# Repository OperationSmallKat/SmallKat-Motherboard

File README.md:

# Esp32-S3 Motherboard

## Pins
|Pin|Use|
|---|---|
| 0| Boot|
| 1| Servo 15|
| 2| Servo 14|
| 3| Servo 13|
| 4| Servo 12|
| 5| Fuse 4 ADC|
| 6| Fuse 1 ADC|
| 7| Servo 0|
| 8| Servo 1|
| 9| Servo 2|
| 10| Servo 3|
| 11| Fuse 2 ADC|
| 12| Servo 4|
| 13| Servo 5|
| 14| Servo 6|
| 15| 6V ADC|
| 16| Batt Voltage ADC|
| 17| Fuse 3 ADC|
| 18| Fuse 5 ADC|
| 19| USB -|
| 20| USB +|
| 21| Servo 7|
| 26| AD Servo 1|
| 33| AD Servo 3|
| 34| AD Servo 4|
| 35| Batt Serial TX|
| 36| Heart Beat LED|
| 37| Servo 8|
| 38| Servo 9|
| 39| Servo 10|
| 40| Servo 11|
| 41| SDA|
| 42| SCL|
| 43| TX|
| 44| RX|
| 45| |
| 46| |
| 47| AD Servo 2|
| 48| Batt Serial RX|

## I2C

  * i2c (SCL 42, SDA 41) - BNO055

## Serial 
  * Serial 0: Tx 43, Rx 44
  * Serial 1: Tx 35, Rx 48

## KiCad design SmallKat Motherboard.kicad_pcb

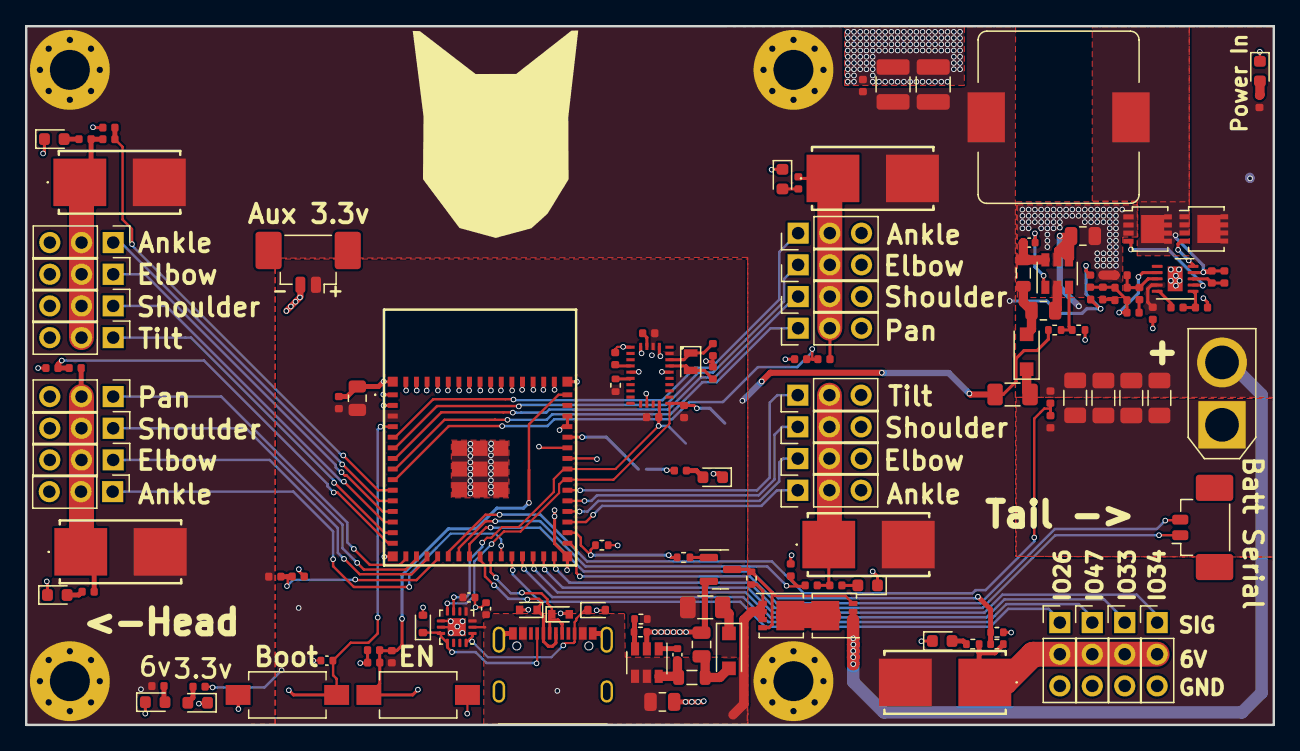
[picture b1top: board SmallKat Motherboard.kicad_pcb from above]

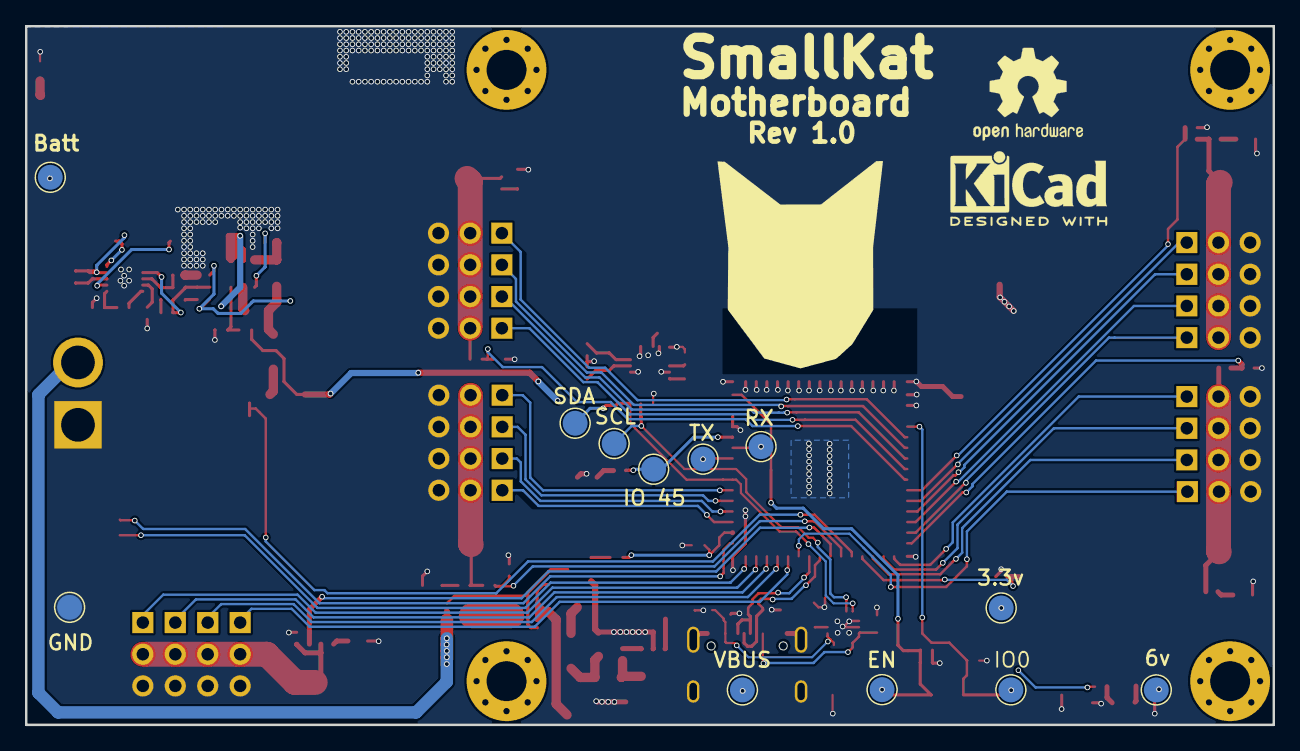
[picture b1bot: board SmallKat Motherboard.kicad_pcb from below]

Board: 2 copper layers, 100.0 x 56.0 mm, 150 parts (12 on the bottom side), 88 nets.

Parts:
AC1: BNO055; BNO085
C1, C3, C12, C14, C18, C22, C23: 0.1uF; C_0402_1005Metric
C2, C5: 2.2uF; C_0805_2012Metric
C4, C6: 10uF; C_0805_2012Metric
C7: 0.1μF; C_0402_1005Metric
C8: 1μF; C_0402_1005Metric
C15, C16: 10pF; C_0402_1005Metric
C17: 22uF; C_0805_2012Metric
C24: 1000pF; C_0402_1005Metric
C25: 100pF; C_0402_1005Metric
C26: 10nF; C_0402_1005Metric
C27, C36: 1uF; C_0402_1005Metric
C28: 4.7uF; C_0402_1005Metric
C29: 470nF; C_0402_1005Metric
C30, C32: 10uF; C_1206_3216Metric
C31, C34: 47uF; C_1206_3216Metric
C33, C35: 100uF; C_1210_3225Metric
D1, D2, D3, D6, D9, D10, D11, D12, D13: LED; LED_0603_1608Metric
D4, D5: DIODE; D_SOD-123F
D7, D8, D14, D17: D_TVS; D_SOD-523
F1, F2, F3, F4, F5: Fuse; 0154500DRTL
F6, F7: Fuse; Fuse_1206_3216Metric
H1, H2, H3, H4: MountingHole_Pad; MountingHole_3.2mm_M3_Pad_Via
IC1, IC2: LMR14010A; SOT-23-6
IC3: TPS40192DRCT-TPS40192DRCT; VSON-10-1EP_3x3mm_P0.5mm_EP1.2x2mm
IC4: ESP32-S3-MINI-1-N8; ESP32S3MINI1N8
J1, J2: BATT_SERIAL; Molex_PicoBlade_53398-0271_1x02-1MP_P1.25mm_Vertical
J3, J4, J5, J6, J9, J10, J11, J12, J13, J14, J15, J16, J17, J18, J19, J20, J21, J22, J23, J24: Conn_01x03_Male; PinHeader_1x03_P2.54mm_Vertical
J8: USB_C_Receptacle; C167321
J25: Conn_01x02_Female; AMASS_XT30U-F_1x02_P5.0mm_Vertical
L1, L2: 10uH; L_0805_2012Metric
L3: 1uH; L_Bourns_SRP1245A
Q1: MMBT3904; SOT-23
Q2, Q3: AON7262E; LFPAK33
Q4, Q5: DMP3017SFG; Diodes_PowerDI3333-8
R1, R16: 330R; R_0402_1005Metric
R2, R4, R7, R10, R13, R15, R17, R19, R20, R23, R24, R27, R30, R33: 10K; R_0402_1005Metric
R3: 2.18K; R_0402_1005Metric
R5, R8, R25, R28, R31, R34: 8.2K; R_0402_1005Metric
R6: 120K; R_0402_1005Metric
R9, R26, R29, R32, R35: 20K; R_0402_1005Metric
R11, R12: 33.2K; R_0402_1005Metric
R21: 10kΩ; R_0402_1005Metric
R22: 2kΩ; R_0402_1005Metric
R36: 2.18k; R_0402_1005Metric
R37: 20k; R_0402_1005Metric
R38: 2.61k; R_0402_1005Metric
R39: 4.22k; R_0402_1005Metric
R40: 12k; R_0402_1005Metric
R41, R42: 100k; R_0402_1005Metric
R43: 1K; R_0402_1005Metric
R44: 100kΩ; R_0402_1005Metric
SW1, SW2: SW_SPST; SW_SPST_EVQPE1
TP1: Check for life; TestPoint_Pad_D2.0mm
TP2: SDA; TestPoint_Pad_D2.0mm
TP3: SCL; TestPoint_Pad_D2.0mm
TP4: 3.3v; TestPoint_Pad_D2.0mm
TP5, TP6, TP7, TP14, TP15: TestPoint; TestPoint_Pad_D2.0mm
TP9: Batt+; TestPoint_Pad_D2.0mm
TP10: GND; TestPoint_Pad_D2.0mm
TP11: 6V; TestPoint_Pad_D2.0mm
U1: FUSB302BMPX; WQFN-14-1EP_2.5x2.5mm_P0.5mm_EP1.45x1.45mm
Y1: 32.768kHz; Crystal_SMD_2012-2Pin_2.0x1.2mm

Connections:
+3V3: AC1.3 (VDD), AC1.28 (VDDIO), C7.1, C8.1, C17.1, C18.1, F6.1, F7.1, IC4.3 (3V3), J2.1, R11.1, R12.1, R15.1, R16.1, R17.1, R19.2, R20.2, R23.1, TP4.1, U1.3 (VDD), U1.4 (VDD)
+6V: C24.1, C33.1, C35.1, C36.1, F1.2, F2.2, F3.2, F4.2, F5.2, H1.1, H2.1, H3.1, H4.1, L3.2, R4.1, R37.1, R43.1, TP11.1
+BATT: C2.1, C27.1, C30.1, C31.1, C32.1, C34.1, IC1.4 (EN), IC1.5 (VIN), IC3.4 (VDD), J25.2, Q2.5 (D), Q5.1 (S), Q5.2 (S), Q5.3 (S), R2.1, R6.1, TP9.1
/MainBoard/AD_6V: F1.1, J3.2, J4.2, J5.2, J6.2, R7.1, R9.1
/MainBoard/AD_SERVO_1: IC4.26 (IO26), J3.1
/MainBoard/AD_SERVO_2: IC4.27 (IO47), J5.1
/MainBoard/AD_SERVO_3: IC4.28 (IO33), J4.1
/MainBoard/AD_SERVO_4: IC4.29 (IO34), J6.1
/MainBoard/BATT_SERIAL_RX: IC4.30 (IO48), J1.1
/MainBoard/BATT_SERIAL_TX: IC4.31 (IO35), J1.2
/MainBoard/BATT_VOLTAGE: IC4.20 (IO16), R2.2, R3.1
/MainBoard/ESP32Module/EN: C22.1, C23.1, IC4.45 (EN), R23.2, SW2.2 (B), TP14.1
/MainBoard/ESP32Module/IO0: C1.1, IC4.4 (IO0), SW1.2 (B), TP15.1
/MainBoard/ESP32Module/IO45: IC4.41 (IO45), R1.1, TP1.1
/MainBoard/ESP32Module/RXD: IC4.40 (RXD0), TP6.1
/MainBoard/ESP32Module/TXD: IC4.39 (TXD0), TP5.1
/MainBoard/IMU/RESET: AC1.11 (NRST), R15.2
/MainBoard/MEASURED_6V: IC4.19 (IO15), R4.2, R5.1
/MainBoard/OUT_CTRL: IC4.32 (IO36), R21.1, R22.1
/MainBoard/SCL: AC1.19 (H_SCL/SCK/RX), IC4.38 (IO42), R19.1, TP3.1, U1.6 (SCL)
/MainBoard/SDA: AC1.20 (H_SDA/H_MISO/TX), IC4.37 (IO41), R20.1, TP2.1, U1.7 (SDA)
/MainBoard/SERVO0: IC4.11 (IO7), J9.1
/MainBoard/SERVO1: IC4.12 (IO8), J11.1
/MainBoard/SERVO2: IC4.13 (IO9), J13.1
/MainBoard/SERVO3: IC4.14 (IO10), J15.1
/MainBoard/SERVO4: IC4.16 (IO12), J17.1
/MainBoard/SERVO5: IC4.17 (IO13), J19.1
/MainBoard/SERVO6: IC4.18 (IO14), J21.1
/MainBoard/SERVO7: IC4.25 (IO21), J23.1
/MainBoard/SERVO8: IC4.33 (IO37), J10.1
/MainBoard/SERVO9: IC4.34 (IO38), J12.1
/MainBoard/SERVO10: IC4.35 (IO39), J14.1
/MainBoard/SERVO11: IC4.36 (IO40), J16.1
/MainBoard/SERVO12: IC4.8 (IO4), J18.1
/MainBoard/SERVO13: IC4.7 (IO3), J20.1
/MainBoard/SERVO14: IC4.6 (IO2), J22.1
/MainBoard/SERVO15: IC4.5 (IO1), J24.1
/MainBoard/Servos/6V1: F2.1, J9.2, J11.2, J13.2, J15.2, R24.1, R26.1
/MainBoard/Servos/6V2: F3.1, J17.2, J19.2, J21.2, J23.2, R27.1, R29.1
/MainBoard/Servos/6V3: F4.1, J10.2, J12.2, J14.2, J16.2, R30.1, R32.1
/MainBoard/Servos/6V4: F5.1, J18.2, J20.2, J22.2, J24.2, R33.1, R35.1
/MainBoard/USB_N: D7.1 (A1), IC4.23 (IO19), J8.A7 (D-), J8.B7 (D-)
/MainBoard/USB_P: D8.1 (A1), IC4.24 (IO20), J8.A6 (D+), J8.B6 (D+)
/MainBoard/USB_PD/CC1: D14.1 (A1), J8.A5 (CC1), U1.10 (CC1), U1.11 (CC1)
/MainBoard/USB_PD/CC2: D17.1 (A1), J8.B5 (CC2), U1.1 (CC2), U1.14 (CC2)
GND: AC1.2 (GND_1), AC1.5 (PS1), AC1.6 (PS0/WAKE), AC1.10 (CLKSEL0), AC1.17 (SA0/H_MOSI), AC1.25 (GND_2), C1.2, C2.2, C4.2, C5.2, C6.2, C7.2, C8.2, C14.1, C15.1, C16.1, C17.2, C18.2, C22.2, C23.2, C27.2, C28.2, C30.2, C31.2, C32.2, C33.2, C34.2, C35.2, C36.2, D1.1 (K), D2.1 (K), D3.1 (K), D6.1 (K), D7.2 (A2), D8.2 (A2), D9.1 (K), D10.1 (K), D11.1 (K), D12.1 (K), D13.1 (K), D14.2 (A2), D17.2 (A2), IC1.2 (GND), IC2.2 (GND), IC3.11 (GND), IC4.1 (GND_1), IC4.2 (GND_2), IC4.42 (GND_3), IC4.43 (GND_4), IC4.46 (GND_5), IC4.47 (GND_6), IC4.48 (GND_7), IC4.49 (GND_8), IC4.50 (GND_9), IC4.51 (GND_10), IC4.52 (GND_11), IC4.53 (GND_12), IC4.54 (GND_13), IC4.55 (GND_14), IC4.56 (GND_15), IC4.57 (GND_16), IC4.58 (GND_17), IC4.59 (GND_18), IC4.60 (GND_19), IC4.61 (GND_20), IC4.62 (GND_21), IC4.63 (GND_22), IC4.64 (GND_23), IC4.65 (GND_24), IC4.66 (GND_25), IC4.67 (GND_26), IC4.68 (GND_27), IC4.69 (GND_28), IC4.70 (GND_29), IC4.71 (GND_30), IC4.72 (GND_31), IC4.73 (GND_32), J2.2, J3.3, J4.3, J5.3, J6.3, J8.A1 (GND), J8.S1 (SHIELD), J9.3, J10.3, J11.3, J12.3, J13.3, J14.3, J15.3, J16.3, J17.3, J18.3, J19.3, J20.3, J21.3, J22.3, J23.3, J24.3, J25.1, Q1.2 (E), Q3.1 (S), Q3.2 (S), Q3.3 (S), R3.2, R5.2, R8.2, R10.1, R13.1, R21.2, R25.2, R28.2, R31.2, R34.2, R36.2, R40.2, SW1.1 (A), SW2.1 (A), TP10.1, U1.8 (GND), U1.9 (GND), U1.15 (GND)
MEASURED_FUSE1: IC4.10 (IO6), R24.2, R25.1
MEASURED_FUSE2: IC4.15 (IO11), R27.2, R28.1
MEASURED_FUSE3: IC4.21 (IO17), R30.2, R31.1
MEASURED_FUSE4: IC4.9 (IO5), R33.2, R34.1
MEASURED_FUSE5: IC4.22 (IO18), R7.2, R8.1
unnamed: AC1.4 (BOOTN), R17.2
unnamed: AC1.9 (CAP), C14.2
unnamed: AC1.27 (XIN32), C15.2, Y1.1
unnamed: AC1.26 (XOUT32/CLKSEL1), C16.2, Y1.2
unnamed: C24.2, R38.2
unnamed: C26.2, R39.1
unnamed: D1.2 (A), R1.2
unnamed: D2.2 (A), R6.2
unnamed: D3.2 (A), R9.2
unnamed: D4.2 (A), F6.2
unnamed: C4.1, D4.1 (K), L1.2
unnamed: D5.2 (A), F7.2
unnamed: C6.1, D5.1 (K), L2.2
unnamed: D6.2 (A), R16.2
unnamed: D9.2 (A), R26.2
unnamed: D10.2 (A), R29.2
unnamed: D11.2 (A), R32.2
unnamed: D12.2 (A), R35.2
unnamed: D13.2 (A), R43.2
unnamed: C12.2, IC1.1 (CB)
unnamed: IC1.3 (FB), R10.2, R12.2
unnamed: C12.1, IC1.6 (SW), L1.1
unnamed: C3.2, IC2.1 (CB)
unnamed: IC2.3 (FB), R11.2, R13.2
unnamed: C3.1, IC2.6 (SW), L2.1
unnamed: C29.2, IC3.8 (BOOT), R42.2
unnamed: C28.1, IC3.6 (BP5), R41.1
unnamed: C25.1, C26.1, IC3.3 (COMP), R40.1
unnamed: C25.2, IC3.2 (FB), R36.1, R37.2, R38.1, R39.2
unnamed: IC3.10 (HDRV), Q2.4 (G)
unnamed: IC3.7 (LDRV), Q3.4 (G)
unnamed: IC3.5 (PGD), R41.2
unnamed: C29.1, IC3.9 (SW), L3.1, Q2.1 (S), Q2.2 (S), Q2.3 (S), Q3.5 (D), R42.1
unnamed: Q1.1 (B), R22.2
unnamed: Q1.3 (C), Q4.4 (G), Q5.4 (G), R44.2
unnamed: Q4.5 (D), Q5.5 (D)
VBUS: C5.1, IC2.4 (EN), IC2.5 (VIN), J8.A4 (VBUS), Q4.1 (S), Q4.2 (S), Q4.3 (S), R44.1, TP7.1, U1.2 (VBUS)

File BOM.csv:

References,Value,Footprint,Quantity,Component Package,Testing Procedures,Procedures,Others,LCSC,Digikey
"C1, C3, C12, C14, C18, C20, C21, C22, C23",0.1uF,C_0402_1005Metric,9,Cut Tape Package,Visual Inspection,Lead-Free(Rohs),Standard Reflow Profile,C1525,
"C15, C16",10pF,C_0402_1005Metric,2,Cut Tape Package,Visual Inspection,Lead-Free(Rohs),Standard Reflow Profile,C32949,
"C19, C28",4.7uF,C_0402_1005Metric,2,Cut Tape Package,Visual Inspection,Lead-Free(Rohs),Standard Reflow Profile,C23733,
"C27, C36",1uF,C_0402_1005Metric,2,Cut Tape Package,Visual Inspection,Lead-Free(Rohs),Standard Reflow Profile,C52923,
C24,1000pF,C_0402_1005Metric,1,Cut Tape Package,Visual Inspection,Lead-Free(Rohs),Standard Reflow Profile,C1523,
C25,100pF,C_0402_1005Metric,1,Cut Tape Package,Visual Inspection,Lead-Free(Rohs),Standard Reflow Profile,C1546,
C26,10nF,C_0402_1005Metric,1,Cut Tape Package,Visual Inspection,Lead-Free(Rohs),Standard Reflow Profile,C15195,
C29,470nF,C_0402_1005Metric,1,Cut Tape Package,Visual Inspection,Lead-Free(Rohs),Standard Reflow Profile,C47339,
"C2, C5",2.2uF,C_0805_2012Metric,2,Cut Tape Package,Visual Inspection,Lead-Free(Rohs),Standard Reflow Profile,C49217,
"C4, C6",10uF,C_0805_2012Metric,2,Cut Tape Package,Visual Inspection,Lead-Free(Rohs),Standard Reflow Profile,C15850,
C17,22uF,C_0805_2012Metric,1,Cut Tape Package,Visual Inspection,Lead-Free(Rohs),Standard Reflow Profile,C45783,
"C30, C32",10uF,C_1206_3216Metric,2,Cut Tape Package,Visual Inspection,Lead-Free(Rohs),Standard Reflow Profile,C13585,
"C31, C34",47uF,C_1206_3216Metric,2,Cut Tape Package,Visual Inspection,Lead-Free(Rohs),Standard Reflow Profile,C96123,
"C33, C35",100uF,C_1210_3225Metric,2,Cut Tape Package,Visual Inspection,Lead-Free(Rohs),Standard Reflow Profile,C15008,
"R2, R4, R7, R10, R13, R14, R17, R18, R19, R20, R21, R22, R23, R24, R27, R30, R33, R44, R45, R46",10K,R_0402_1005Metric,20,Cut Tape Package,Visual Inspection,Lead-Free(Rohs),Standard Reflow Profile,C25744,
"R5, R8, R25, R28, R31, R34",8.2K,R_0402_1005Metric,6,Cut Tape Package,Visual Inspection,Lead-Free(Rohs),Standard Reflow Profile,C25924,
"R9, R26, R29, R32, R35, R37",20K,R_0402_1005Metric,6,Cut Tape Package,Visual Inspection,Lead-Free(Rohs),Standard Reflow Profile,C25765,
"R1, R16",330R,R_0402_1005Metric,2,Cut Tape Package,Visual Inspection,Lead-Free(Rohs),Standard Reflow Profile,C25104,
"R11, R12",33.2K,R_0402_1005Metric,2,Cut Tape Package,Visual Inspection,Lead-Free(Rohs),Standard Reflow Profile,C122548,
"R41, R42",100k,R_0402_1005Metric,2,Cut Tape Package,Visual Inspection,Lead-Free(Rohs),Standard Reflow Profile,C25741,
R3,2.4K,R_0402_1005Metric,1,Cut Tape Package,Visual Inspection,Lead-Free(Rohs),Standard Reflow Profile,C25882,
R6,120K,R_0402_1005Metric,1,Cut Tape Package,Visual Inspection,Lead-Free(Rohs),Standard Reflow Profile,C25750,
R36,2.18k,R_0402_1005Metric,1,Cut Tape Package,Visual Inspection,Lead-Free(Rohs),Standard Reflow Profile,C25879,
R38,2.61k,R_0402_1005Metric,1,Cut Tape Package,Visual Inspection,Lead-Free(Rohs),Standard Reflow Profile,C34906,
R39,4.22k,R_0402_1005Metric,1,Cut Tape Package,Visual Inspection,Lead-Free(Rohs),Standard Reflow Profile,C25898,
R40,12k,R_0402_1005Metric,1,Cut Tape Package,Visual Inspection,Lead-Free(Rohs),Standard Reflow Profile,C25752,
R43,1K,R_0402_1005Metric,1,Cut Tape Package,Visual Inspection,Lead-Free(Rohs),Standard Reflow Profile,C11702,
"L1, L2",10uH,L_0805_2012Metric,2,Cut Tape Package,Visual Inspection,Lead-Free(Rohs),Standard Reflow Profile,C280489,
L3,1uH,L_Bourns_SRP1245A,1,Cut Tape Package,Visual Inspection,Lead-Free(Rohs),Standard Reflow Profile,C208109,
"D4, D5",DIODE,D_SOD-123F,2,Cut Tape Package,Visual Inspection,Lead-Free(Rohs),Standard Reflow Profile,C8598,
"D7, D8",D_TVS,D_SOD-523,2,Cut Tape Package,Visual Inspection,Lead-Free(Rohs),Standard Reflow Profile,C136171,
D1,LED,LED_0603_1608Metric,1,Cut Tape Package,Visual Inspection,Lead-Free(Rohs),Standard Reflow Profile, C142305,
"D2, D3, D6, D9, D10, D11, D12, D13",LED,LED_0603_1608Metric,9,Cut Tape Package,Visual Inspection,Lead-Free(Rohs),Standard Reflow Profile,C72043,
U3,ESP32-WROOM-32,ESP32-WROOM-32,1,Cut Tape Package,Visual Inspection,Lead-Free(Rohs),Standard Reflow Profile,C328062,
U2,BNO055,LGA-28_5.2x3.8mm_P0.5mm,1,Cut Tape Package,Visual Inspection,Lead-Free(Rohs),Standard Reflow Profile,C93216,
U4,CP2102N-A01-GQFN24,QFN-24-1EP_4x4mm_P0.5mm_EP2.6x2.6mm,1,Cut Tape Package,Visual Inspection,Lead-Free(Rohs),Standard Reflow Profile,,336-5888-2-ND
U1,PCA9685BS,QFN-28-1EP_6x6mm_P0.65mm_EP4.25x4.25mm,1,Cut Tape Package,Visual Inspection,Lead-Free(Rohs),Standard Reflow Profile,,568-5305-2-ND 
Y1,32.768kHz,Crystal_SMD_3215-2Pin_3.2x1.5mm,1,Cut Tape Package,Visual Inspection,Lead-Free(Rohs),Standard Reflow Profile,C32346,
"F1, F2, F3, F4, F5",Fuse,0154.250DR,5,Cut Tape Package,Visual Inspection,Lead-Free(Rohs),Standard Reflow Profile,C108518,
"F6, F7",Fuse,Fuse_1210_3225Metric,2,Cut Tape Package,Visual Inspection,Lead-Free(Rohs),Standard Reflow Profile,C70076,
"SW1, SW2",SW_SPST,SW_SPST_EVQPE1,2,Cut Tape Package,Visual Inspection,Lead-Free(Rohs),Standard Reflow Profile,C318938,
"IC1, IC2",LMR14010A,SOT-23-6,2,Cut Tape Package,Visual Inspection,Lead-Free(Rohs),Standard Reflow Profile,C388174,
Q1,MBT3904DW1,SOT-363_SC-70-6,1,Cut Tape Package,Visual Inspection,Lead-Free(Rohs),Standard Reflow Profile,C131781,
IC3,TPS40192DRCT-TPS40192DRCT,VSON-10-1EP_3x3mm_P0.5mm_EP1.2x2mm,1,Cut Tape Package,Visual Inspection,Lead-Free(Rohs),Standard Reflow Profile,C14972,
"Q2, Q3",BUK9M17-30EX / BUK7M10-40E,VSON-8_3.3x3.3mm_P0.65mm_NexFET,2,Cut Tape Package,Visual Inspection,Lead-Free(Rohs),Standard Reflow Profile, C458171,
J8,USB_C_Receptacle,C167321,1,Cut Tape Package,Visual Inspection,Lead-Free(Rohs),Standard Reflow Profile,C167321,
"J1, J2, J26, J27, J28, J29",Qwiic connector,JST_SH_SM04B-SRSS-TB_1x04-1MP_P1.00mm_Horizontal,6,Cut Tape Package,Visual Inspection,Lead-Free(Rohs),Standard Reflow Profile,,1568-PRT-16766-ND
"J3, J4, J5, J6, J9, J10, J11, J12, J13, J14, J15, J16, J17, J18, J19, J20, J21, J22, J23, J24",Conn_01x03_Male,PinHeader_1x03_P2.54mm_Vertical,20,Tube Package,Visual Inspection,Lead-Free(Rohs),Standard Reflow Profile,C49257,
J7,Micro_SD_Card,microSD_HC_Molex_104031-0811,1,Cut Tape Package,Visual Inspection,Lead-Free(Rohs),Standard Reflow Profile,C585350,

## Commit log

2019-02-08 First routing rev
2019-02-08 Removed n neessary files
2019-02-22 Updated to use BECs and added silkscreen
2019-04-04 Updated to use nucleo l432kc
2019-11-09 init
2019-11-09 Workign Revision
2019-11-22 In progress of charging implimentation
2019-11-23 Routing done
2019-11-23 PDFs
2020-01-28 Added STEP model for max34409e
2020-01-28 Updated footprints with STEP model
2020-01-28 pulled fuse FP into local proj libraries and added STEP
2020-01-28 Changed FP lib to local copy, updated board
2020-01-28 Moved usb footprint into local library
2020-01-28 Use new local FP lib
2020-01-28 Added STEP model for USBC
2020-01-28 Add step to FP
2020-01-28 swapped to local FP
2020-01-28 SRP1245A into a local lib
2020-01-28 Updated inductor FP
2020-01-28 added step model for indiuctor
2020-01-28 Added interactive bom
2020-01-28 Updated footprints
2020-01-28 Added STEP model for board
2020-02-12 order
2020-11-29 This rev removes the safety micro and instead uses the dji battery
2020-12-03 batt connector and all in the right place. has not been ordered, waiting for prev rev to be tested first
2020-12-06 rev, pendingorder
2020-12-17 rev ordered
2021-01-15 Final order version with all bom files
2021-01-23 Ready to order
2021-03-11 order files
2021-03-11 ordered version with foot connecotrs
2022-12-31 fully routed, currently 4 layers, ordered 2 layer version with only middle 2 layers removed
2022-12-31 cleaning up old files
2022-12-31 Updating readme
2022-12-31 fixing i2c pins to not be on strapping pins
2023-01-14 Addressing the issues with the sample version, Updating the bom to source all the correct components from the JLCPCB supply
2023-03-13 Adding usb c pd negotiation for battery charging
